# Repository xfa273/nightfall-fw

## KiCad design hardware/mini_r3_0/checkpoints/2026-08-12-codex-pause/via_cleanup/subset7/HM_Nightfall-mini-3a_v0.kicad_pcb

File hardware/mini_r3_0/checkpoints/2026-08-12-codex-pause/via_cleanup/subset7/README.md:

# Integration-safe 7-item drill-in-pad cleanup subset

This subset intentionally excludes the supply/CS-sensitive C_MCU1.2,
C_MCU2.2, C_MCU-M0.2, U4.8, and R33.2 items.

Cleaned items: UBUZ0.2, Q3.2, C7.1, R1FR0.1, R2R0.2, C8.2, Q3.3.

Verified on the fan handoff:

- exact KiCad physical DRC errors: 0
- drill-in-pad overlaps: 5, exactly the five intentionally deferred items
- KiCad unconnected count: 32 (unchanged from input)
- GND groups: 1; GND2 groups: 1
- zone self/cross-edge incidents: 0

Replay with `apply_independent_cleanup.py` using canonical-named project
copies, then run exact refill/DRC/audit again on the integrated board.

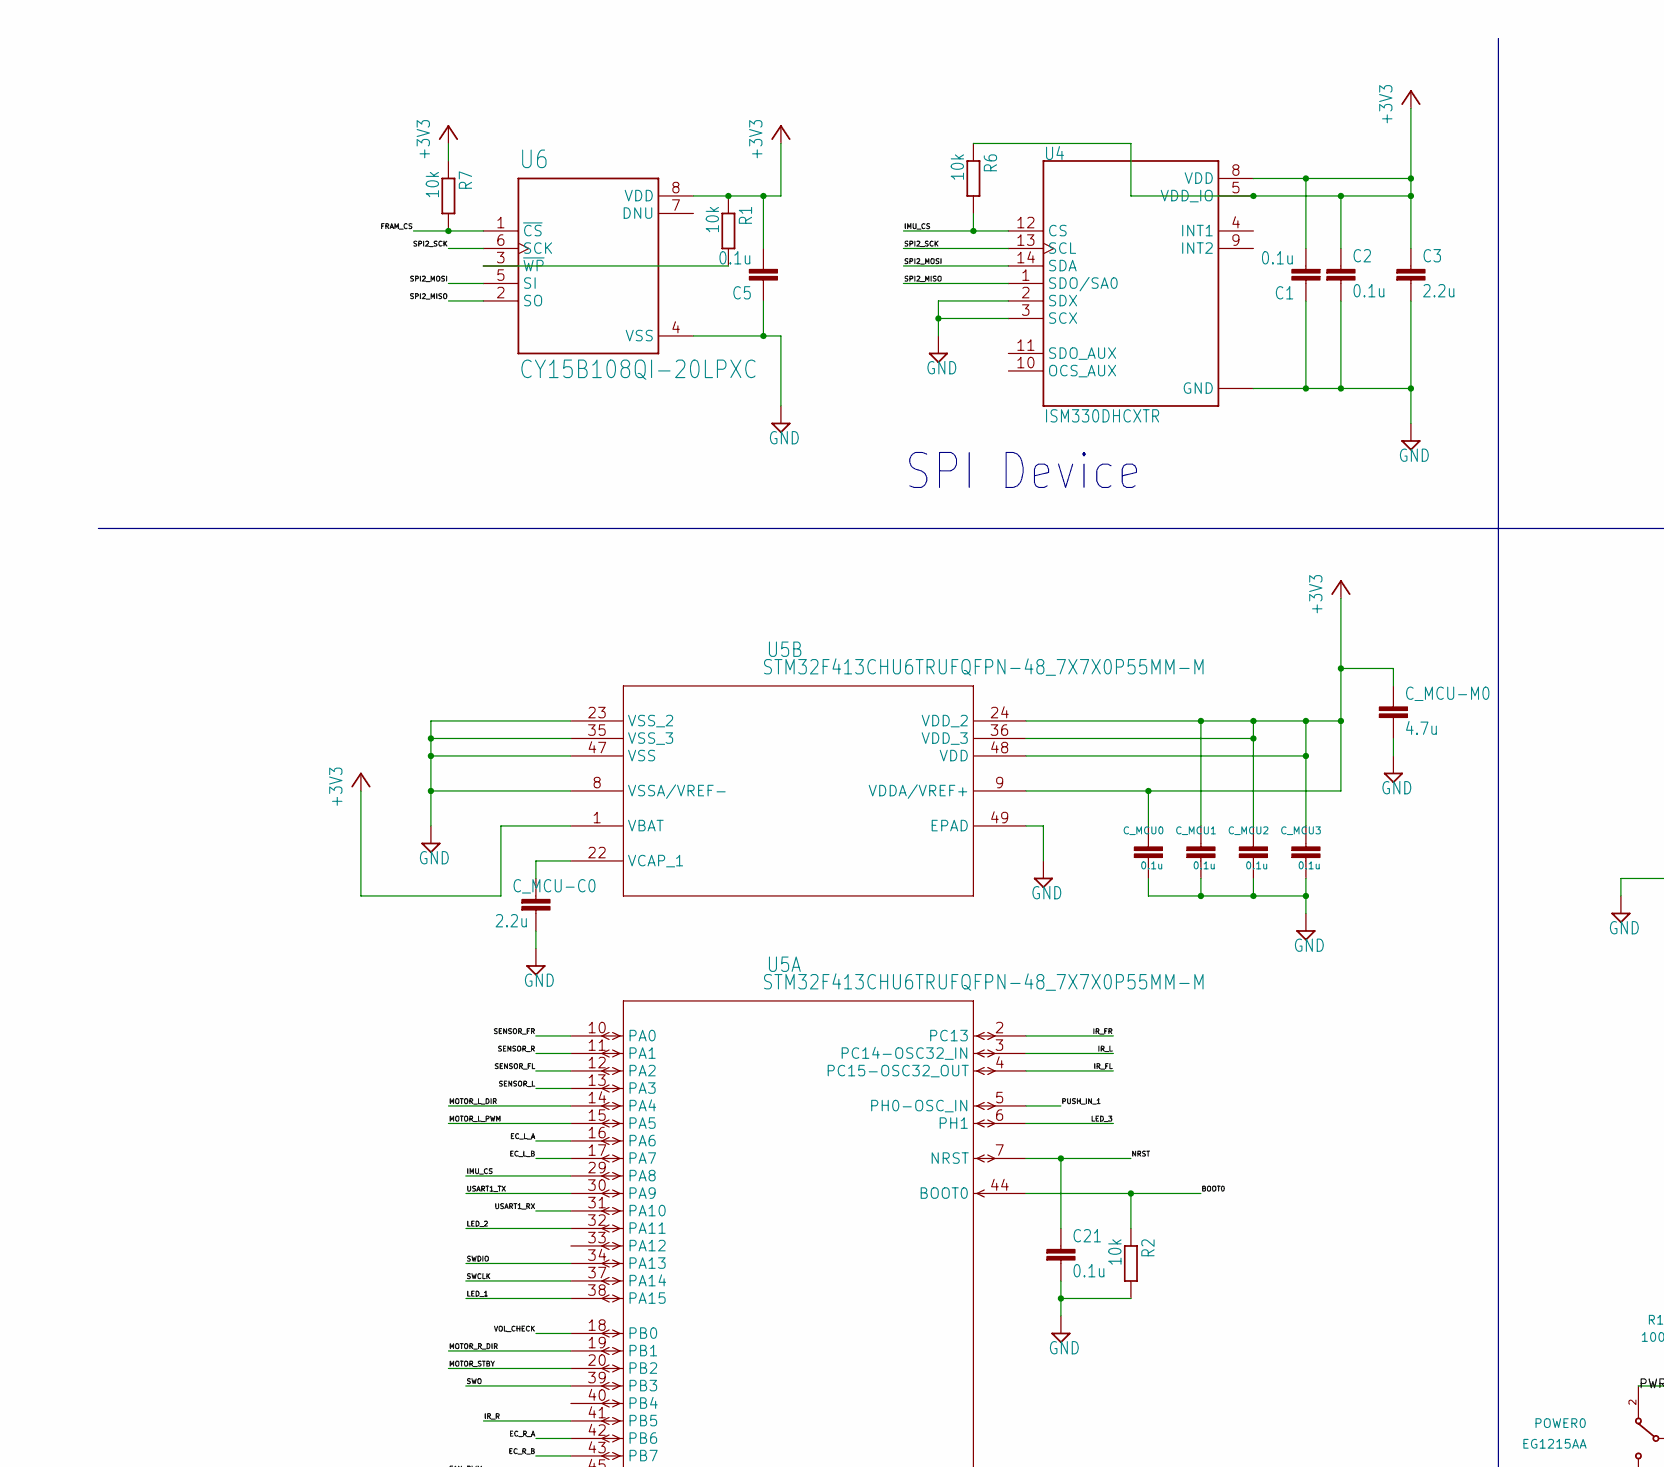
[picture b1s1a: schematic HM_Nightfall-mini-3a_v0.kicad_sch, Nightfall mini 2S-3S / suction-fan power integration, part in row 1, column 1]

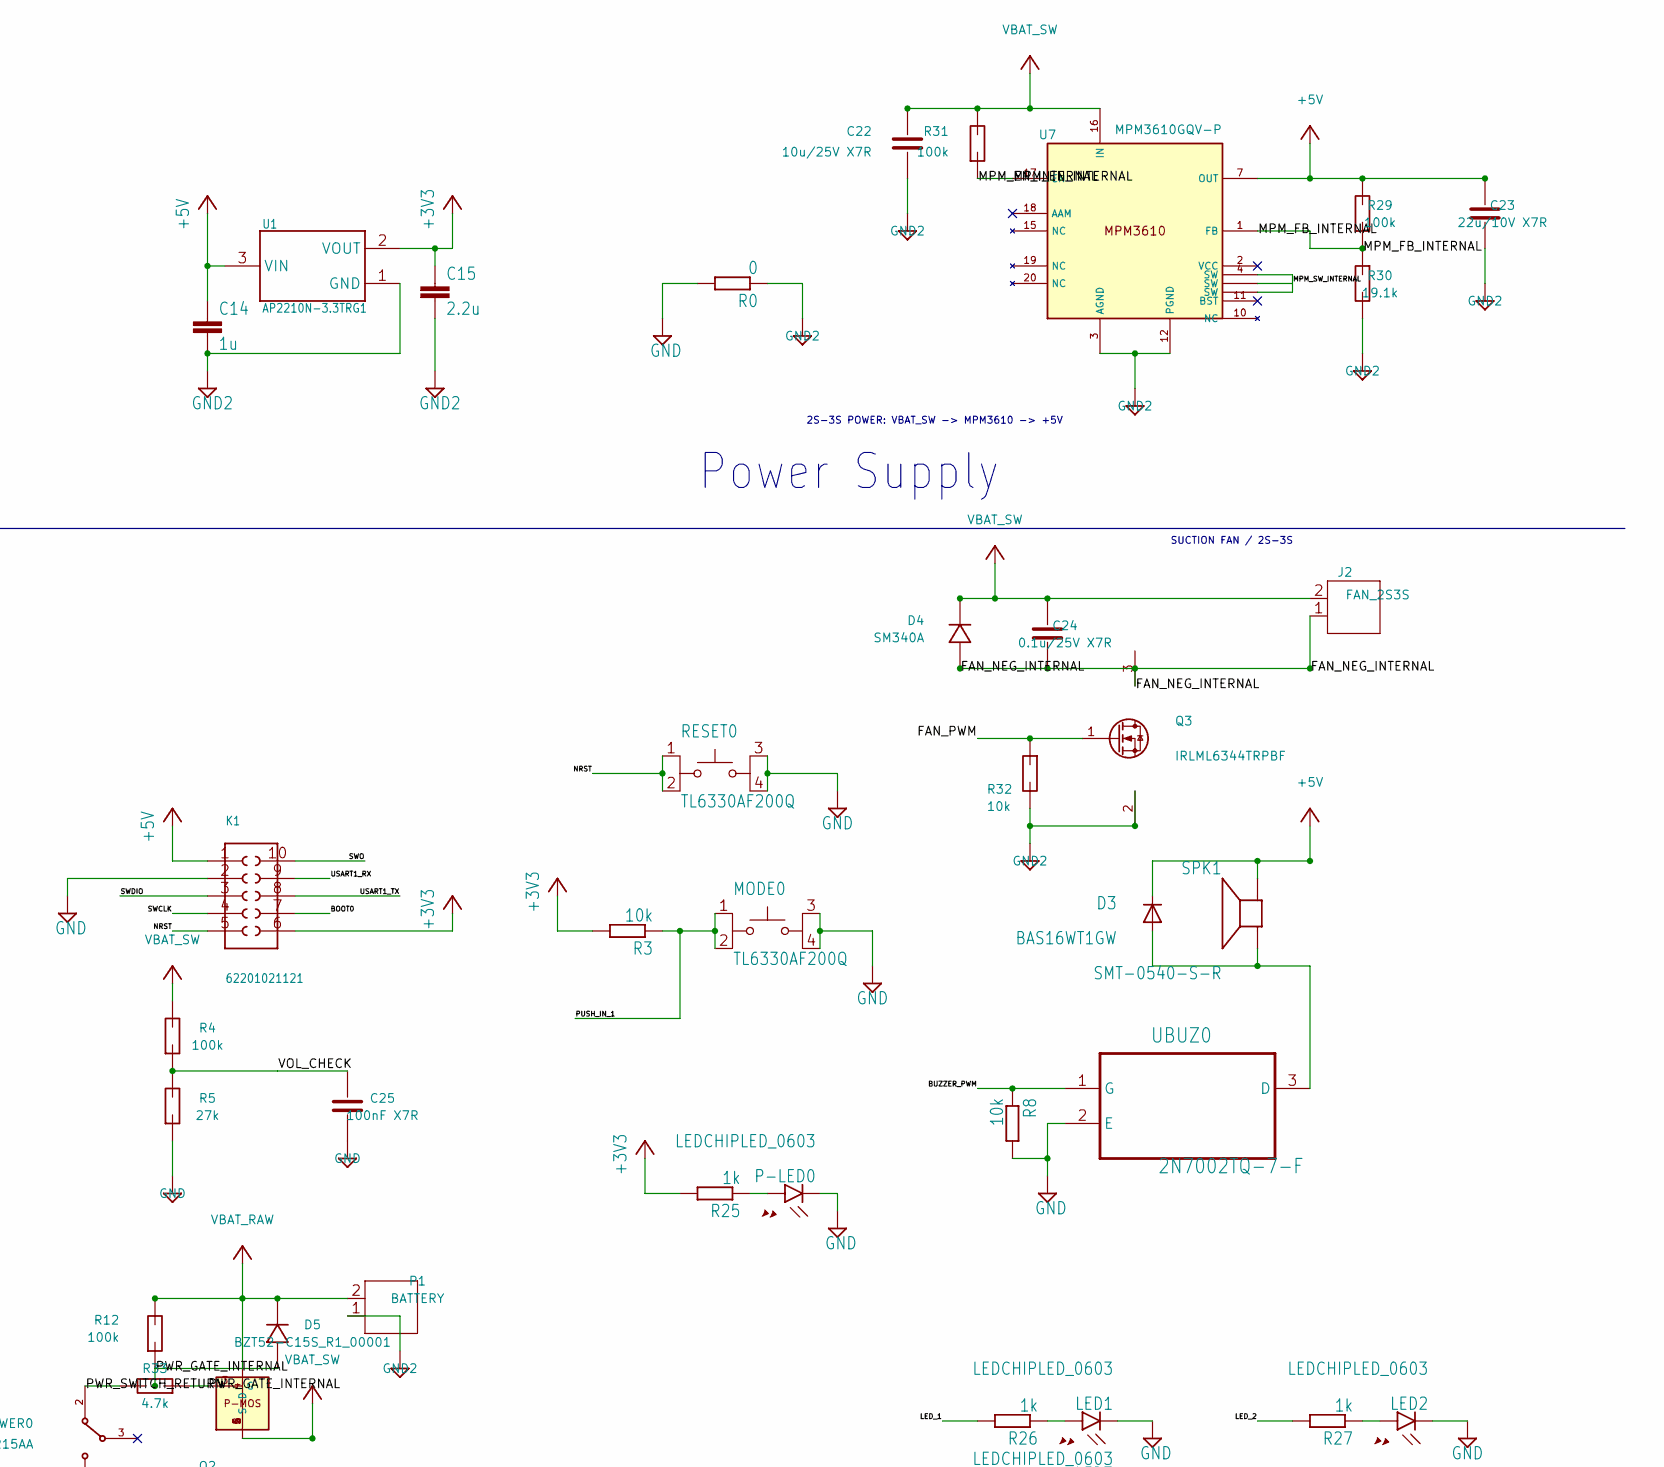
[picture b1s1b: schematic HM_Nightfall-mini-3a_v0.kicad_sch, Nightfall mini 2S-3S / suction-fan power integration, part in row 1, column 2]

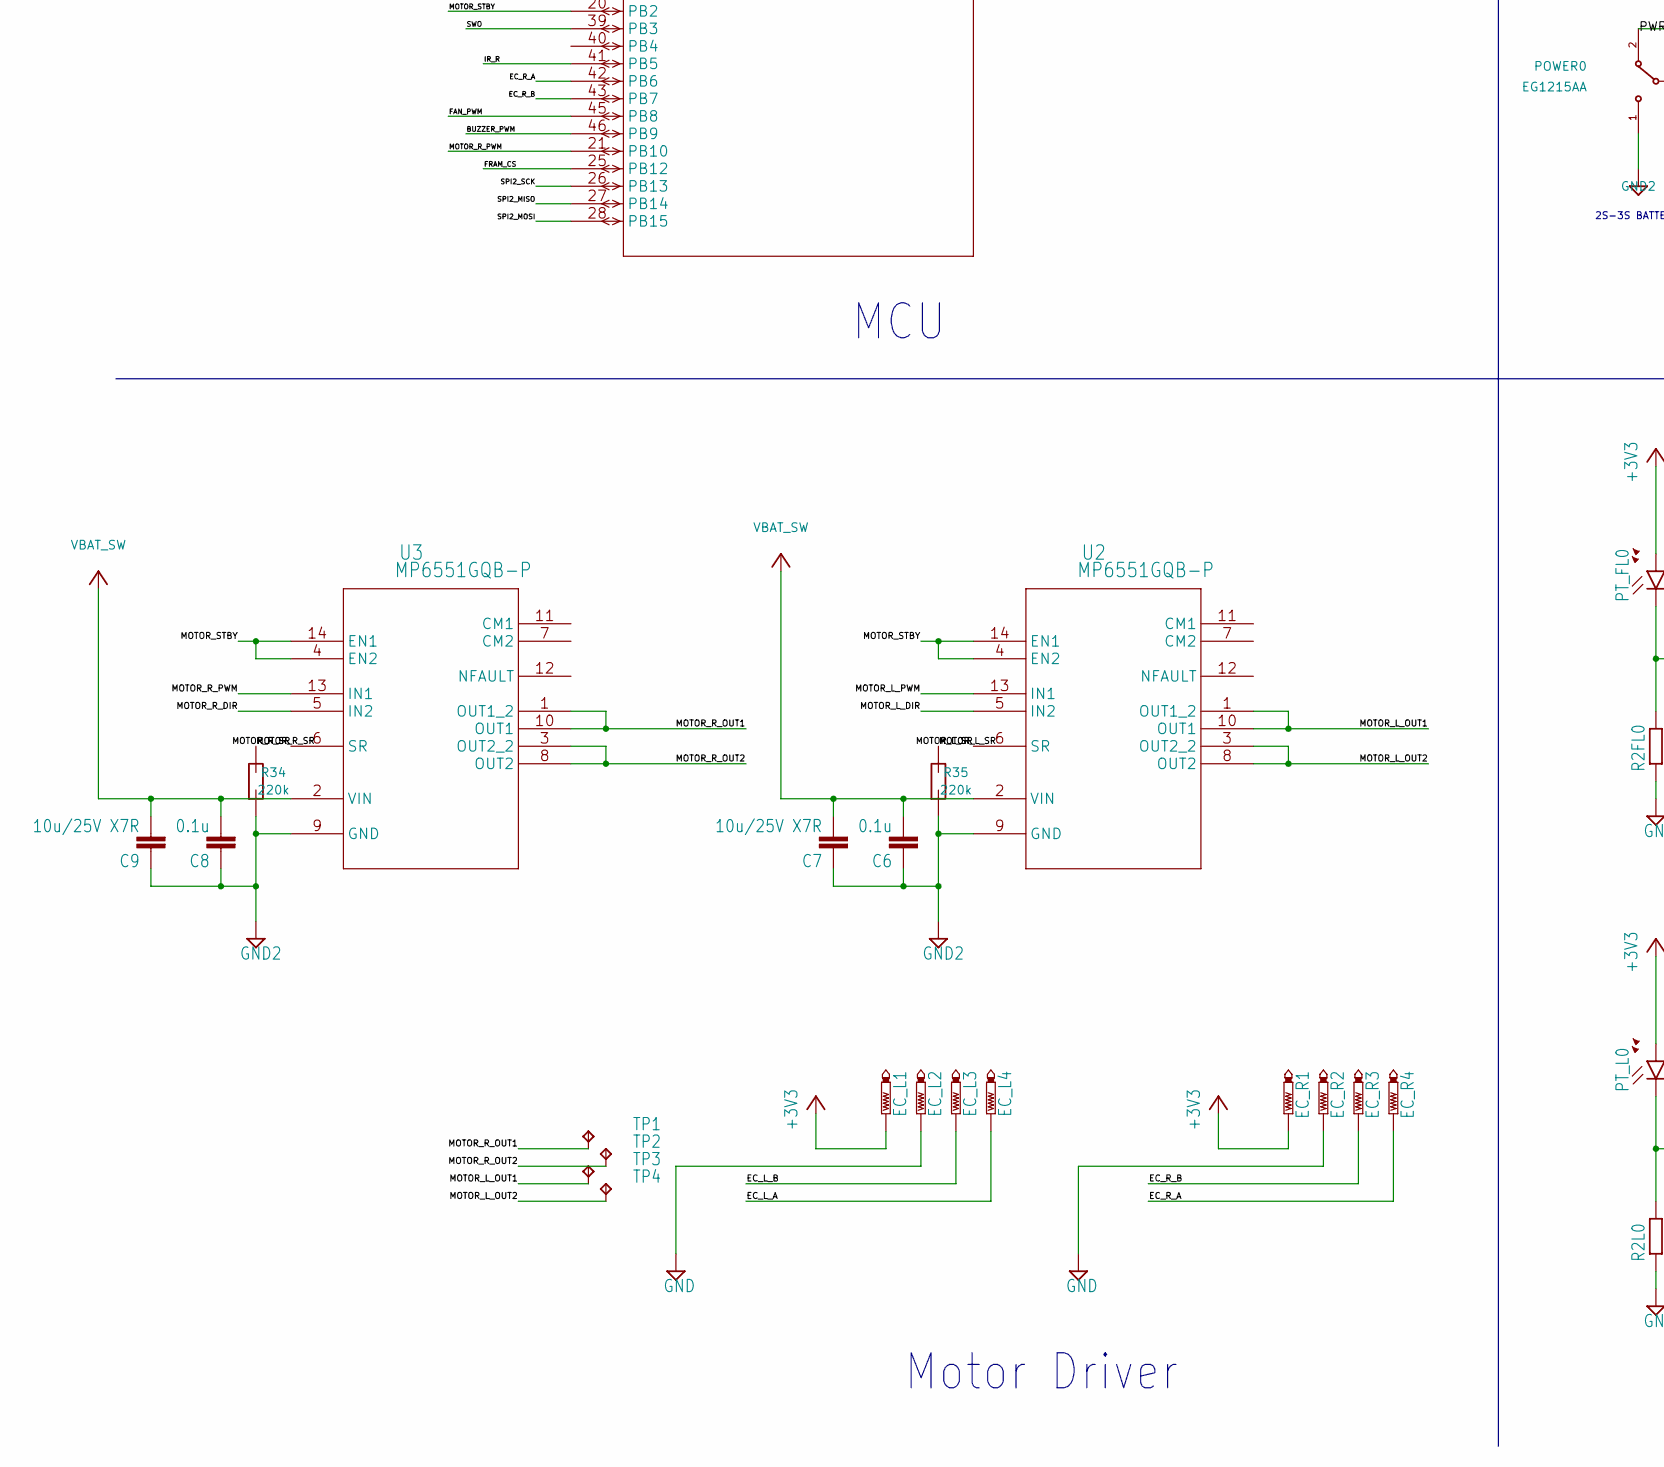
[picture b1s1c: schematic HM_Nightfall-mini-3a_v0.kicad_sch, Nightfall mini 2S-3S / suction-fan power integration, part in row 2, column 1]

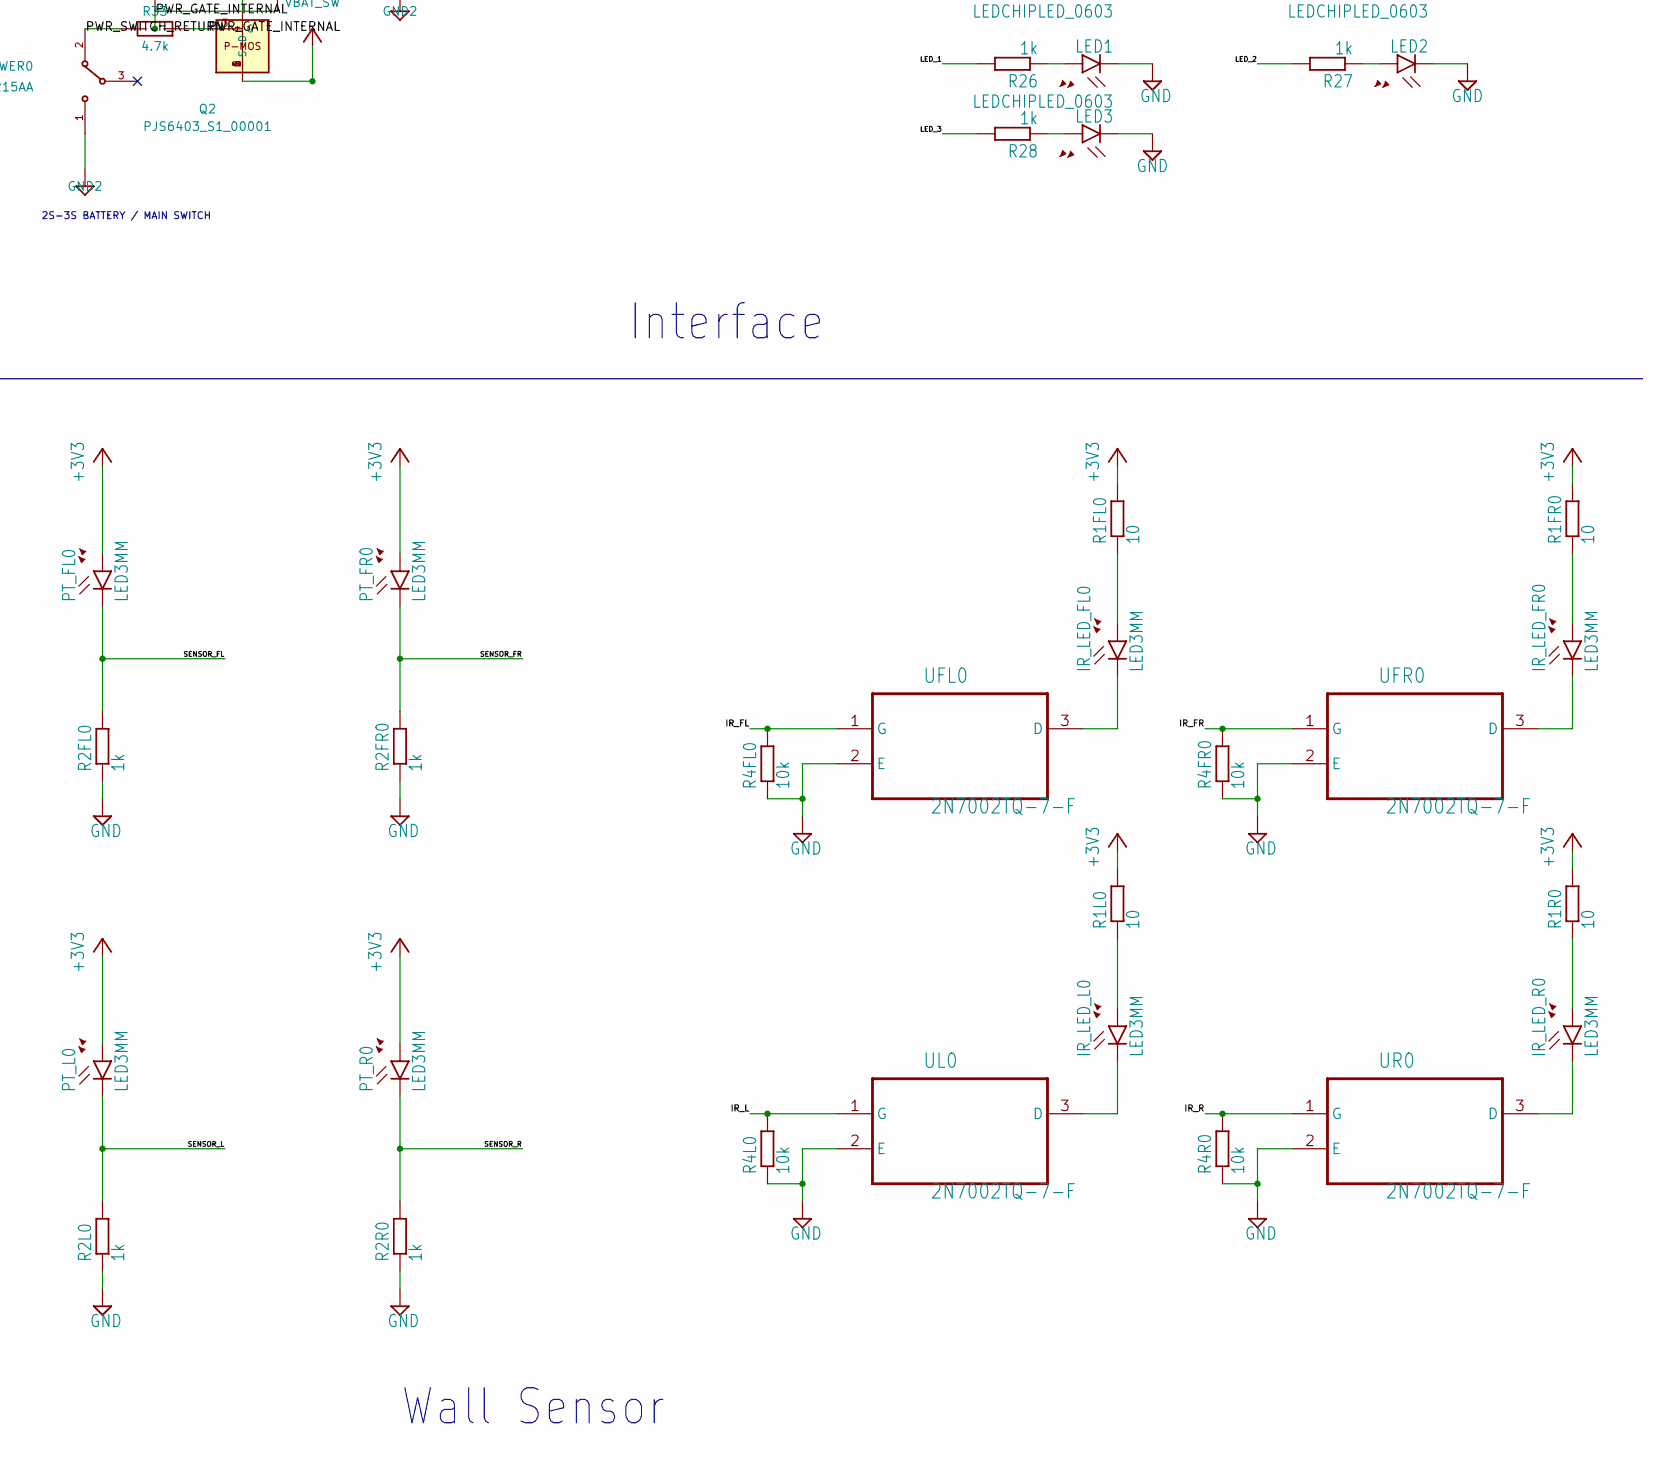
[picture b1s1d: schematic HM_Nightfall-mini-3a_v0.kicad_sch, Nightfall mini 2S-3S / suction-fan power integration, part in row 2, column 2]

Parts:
C1, C2, C5, C6, C8, C21: 0.1u; C0402
C3, C15: 2.2u; C0402
C7, C9, C22: 10u/25V X7R; C_0805_2012Metric
C14: 1u; C0402
C23: 22u/10V X7R; C_0805_2012Metric
C24: 0.1u/25V X7R; C_0402_1005Metric
C25: 100nF X7R; C_0402_1005Metric
C_MCU0, C_MCU2, C_MCU3: 0.1u; C0402
C_MCU1: 0.1u; C_0402_1005Metric
C_MCU-C0: 2.2u; C_0402_1005Metric
C_MCU-M0: 4.7u; C0402
D3: BAS16WT1GW; SOT323
D4: SM340A; D_SMA
D5: BZT52-C15S_R1_00001; D_SOD-323
EC_L1, EC_L2, EC_L3, EC_L4: PTR1TP06SQ; TP06SQ
EC_R1, EC_R2, EC_R3, EC_R4: PTR1TP06SQ; TP06SQ
IR_LED_FL0: LED3MM
IR_LED_FR0: LED3MM
IR_LED_L0: LED3MM
IR_LED_R0: LED3MM
J2: FAN_2S3S; FAN_WIRE_PADS_2P
K1: 62201021121
LED1, LED2, LED3: LEDCHIPLED_0603; CHIPLED_0603
MODE0: TL6330AF200Q; SW_TL6330AF200Q
P1: BATTERY; JST_PH2
P-LED0: LEDCHIPLED_0603; CHIPLED_0603
POWER0: EG1215AA; SW_EG1215AA
PT_FL0: LED3MM
PT_FR0: LED3MM
PT_L0: LED3MM
PT_R0: LED3MM
Q2: PJS6403_S1_00001; SOT-23-6
Q3: IRLML6344TRPBF; SOT-23
R0: 0; R0402
R1, R2, R3, R4FL0, R4FR0, R4L0, R4R0, R6, R7, R8: 10k; R0402
R1FL0, R1FR0, R1L0, R1R0: 10; R0402
R2FL0, R2FR0, R2L0, R2R0, R26, R27, R28: 1k; R0402
R4, R12: 100k; R0402
R5: 27k; R0402
R25: 1k; R_0402_1005Metric
R29, R31: 100k; R_0402_1005Metric
R30: 19.1k; R_0402_1005Metric
R32: 10k; R_0402_1005Metric
R33: 4.7k; R0402
R34, R35: 220k; R_0402_1005Metric
RESET0: TL6330AF200Q; SW_TL6330AF200Q
SPK1: SMT-0540-S-R
TP1, TP2, TP3, TP4: TPB1,27; B1,27
U1: AP2210N-3.3TRG1; SOT95P280X145-3N
U2, U3: MP6551GQB-P; QFN-14_MP6551_MNP
U4: ISM330DHCXTR; PQFN50P250X300X86-14N
U5: STM32F413CHU6TRUFQFPN-48_7X7X0P55MM-M; UFQFPN-48_7X7X0P55MM-M_noEP_hand_solder
U6: CY15B108QI-20LPXC; SON65P328X323X55-8N
U7: MPM3610GQV-P; MPM3610_QFN-20_3x5mm
UBUZ0: 2N7002TQ-7-F; SOT50P160X90-3N
UFL0: 2N7002TQ-7-F; SOT50P160X90-3N
UFR0: 2N7002TQ-7-F; SOT50P160X90-3N
UL0: 2N7002TQ-7-F; SOT50P160X90-3N
UR0: 2N7002TQ-7-F; SOT50P160X90-3N

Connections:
+3V3: C1.2, C2.1, C3.1, C5.2, C15.1, C_MCU0.1, C_MCU1.1, C_MCU2.1, C_MCU3.1, C_MCU-M0.1, EC_L1.TP (TP_TP), EC_R1.TP (TP_TP), K1.6, PT_FL0.A, PT_FR0.A, PT_L0.A, PT_R0.A, R1.1, R1FL0.2, R1FR0.2, R1L0.2, R1R0.2, R3.2, R6.1, R7.1, R25.2, U1.2 (VOUT), U4.5 (VDD_IO), U4.8 (VDD), U5.1 (VBAT), U5.9 (VDDA/VREF+), U5.24 (VDD_2), U5.36 (VDD_3), U5.48 (VDD), U6.8 (VDD)
+5V: C14.1, C23.1, D3.3 (K), K1.1, R29.2, SPK1.+ (-), U1.3 (VIN), U7.7 (OUT), U7.8 (OUT), U7.9 (OUT)
/BOOT0: K1.7, R2.1, U5.44 (BOOT0)
/BUZZER_PWM: R8.1, U5.46 (PB9), UBUZ0.1 (G)
/EC_L_A: EC_L4.TP (TP_TP), U5.16 (PA6)
/EC_L_B: EC_L3.TP (TP_TP), U5.17 (PA7)
/EC_R_A: EC_R4.TP (TP_TP), U5.42 (PB6)
/EC_R_B: EC_R3.TP (TP_TP), U5.43 (PB7)
/FAN_NEG_INTERNAL: C24.2, D4.1 (A), J2.1, Q3.3 (D)
/FAN_PWM: Q3.1 (G), R32.1, U5.45 (PB8)
/IR_FL: R4FL0.2, U5.4 (PC15-OSC32_OUT), UFL0.1 (G)
/IR_FR: R4FR0.2, U5.2 (PC13), UFR0.1 (G)
/IR_L: R4L0.2, U5.3 (PC14-OSC32_IN), UL0.1 (G)
/IR_R: R4R0.2, U5.41 (PB5), UR0.1 (G)
/LED_1: R26.2, U5.38 (PA15)
/LED_2: R27.2, U5.32 (PA11)
/LED_3: R28.2, U5.6 (PH1)
/MOTOR_L_DIR: U2.5 (IN2), U5.14 (PA4)
/MOTOR_L_OUT1: TP3.TP (TP_TP), U2.1 (OUT1_2), U2.10 (OUT1)
/MOTOR_L_OUT2: TP4.TP (TP_TP), U2.3 (OUT2_2), U2.8 (OUT2)
/MOTOR_L_PWM: U2.13 (IN1), U5.15 (PA5)
/MOTOR_L_SR: R35.2, U2.6 (SR)
/MOTOR_R_DIR: U3.5 (IN2), U5.19 (PB1)
/MOTOR_R_OUT1: TP1.TP (TP_TP), U3.1 (OUT1_2), U3.10 (OUT1)
/MOTOR_R_OUT2: TP2.TP (TP_TP), U3.3 (OUT2_2), U3.8 (OUT2)
/MOTOR_R_PWM: U3.13 (IN1), U5.21 (PB10)
/MOTOR_R_SR: R34.2, U3.6 (SR)
/MOTOR_STBY: U2.4 (EN2), U2.14 (EN1), U3.4 (EN2), U3.14 (EN1), U5.20 (PB2)
/MPM_EN_INTERNAL: R31.1, U7.17 (EN)
/MPM_FB_INTERNAL: R29.1, R30.1, U7.1 (FB)
/MPM_SW_INTERNAL: U7.4 (SW), U7.5 (SW), U7.6 (SW)
/NRST: C21.1, K1.5, RESET0.1, RESET0.2, U5.7 (NRST)
/PUSH_IN_1: MODE0.1, MODE0.2, R3.1, U5.5 (PH0-OSC_IN)
/PWR_GATE_INTERNAL: D5.1 (A), Q2.3 (G), R12.1, R33.1
/PWR_SWITCH_RETURN: POWER0.2 (COM), R33.2
/SENSOR_FL: PT_FL0.K (C), R2FL0.2, U5.12 (PA2)
/SENSOR_FR: PT_FR0.K (C), R2FR0.2, U5.10 (PA0)
/SENSOR_L: PT_L0.K (C), R2L0.2, U5.13 (PA3)
/SENSOR_R: PT_R0.K (C), R2R0.2, U5.11 (PA1)
/SPI2_MISO: U4.1 (SDO/SA0), U5.27 (PB14), U6.2 (SO)
/SPI2_MOSI: U4.14 (SDA), U5.28 (PB15), U6.5 (SI)
/SPI2_SCK: U4.13 (SCL), U5.26 (PB13), U6.6 (SCK)
/SWCLK: K1.4, U5.37 (PA14)
/SWDIO: K1.3, U5.34 (PA13)
/SWO: K1.10, U5.39 (PB3)
/USART1_RX: K1.9, U5.31 (PA10)
/USART1_TX: K1.8, U5.30 (PA9)
/VOL_CHECK: C25.1, R4.1, R5.2, U5.18 (PB0)
GND: C1.1, C2.2, C3.2, C5.1, C21.2, C25.2, C_MCU0.2, C_MCU1.2, C_MCU2.2, C_MCU3.2, C_MCU-C0.2, C_MCU-M0.2, EC_L2.TP (TP_TP), EC_R2.TP (TP_TP), K1.2, LED1.C, LED2.C, LED3.C, MODE0.3, MODE0.4, P-LED0.C, R0.2, R2.2, R2FL0.1, R2FR0.1, R2L0.1, R2R0.1, R4FL0.1, R4FR0.1, R4L0.1, R4R0.1, R5.1, R8.2, RESET0.3, RESET0.4, U4.2 (SDX), U4.3 (SCX), U4.6 (GND), U4.7 (GND), U5.8 (VSSA/VREF-), U5.23 (VSS_2), U5.35 (VSS_3), U5.47 (VSS), U5.49 (EPAD), U6.4 (VSS), UBUZ0.2 (E), UFL0.2 (E), UFR0.2 (E), UL0.2 (E), UR0.2 (E)
GND2: C6.1, C7.1, C8.1, C9.1, C14.2, C15.2, C22.2, C23.2, P1.1, POWER0.1 (OFF), Q3.2 (S), R0.1, R30.2, R32.2, R34.1, R35.1, U1.1 (GND), U2.9 (GND), U3.9 (GND), U7.3 (AGND), U7.12 (PGND), U7.13 (PGND), U7.14 (PGND)
unnamed: D3.1 (A), SPK1.- (+), UBUZ0.3 (D)
unnamed: IR_LED_FL0.K (C), UFL0.3 (D)
unnamed: IR_LED_FL0.A, R1FL0.1
unnamed: IR_LED_FR0.K (C), UFR0.3 (D)
unnamed: IR_LED_FR0.A, R1FR0.1
unnamed: IR_LED_L0.K (C), UL0.3 (D)
unnamed: IR_LED_L0.A, R1L0.1
unnamed: IR_LED_R0.K (C), UR0.3 (D)
unnamed: IR_LED_R0.A, R1R0.1
unnamed: LED1.A, R26.1
unnamed: LED2.A, R27.1
unnamed: LED3.A, R28.1
unnamed: P-LED0.A, R25.1
unnamed: C_MCU-C0.1, U5.22 (VCAP_1)
unnamed: R1.2, U6.3 (~WP)
VBAT_RAW: D5.2 (K), P1.2, Q2.4 (S), R12.2
VBAT_SW: C6.2, C7.2, C8.2, C9.2, C22.1, C24.1, D4.2 (K), J2.2, Q2.1 (D), Q2.2 (D), Q2.5 (D), Q2.6 (D), R4.2, R31.2, U2.2 (VIN), U3.2 (VIN), U7.16 (IN)

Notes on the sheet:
Wall Sensor
MCU
Power Supply
SPI Device
Interface
Motor Driver
2S-3S POWER: VBAT_SW -> MPM3610 -> +5V
SUCTION FAN / 2S-3S
2S-3S BATTERY / MAIN SWITCH

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
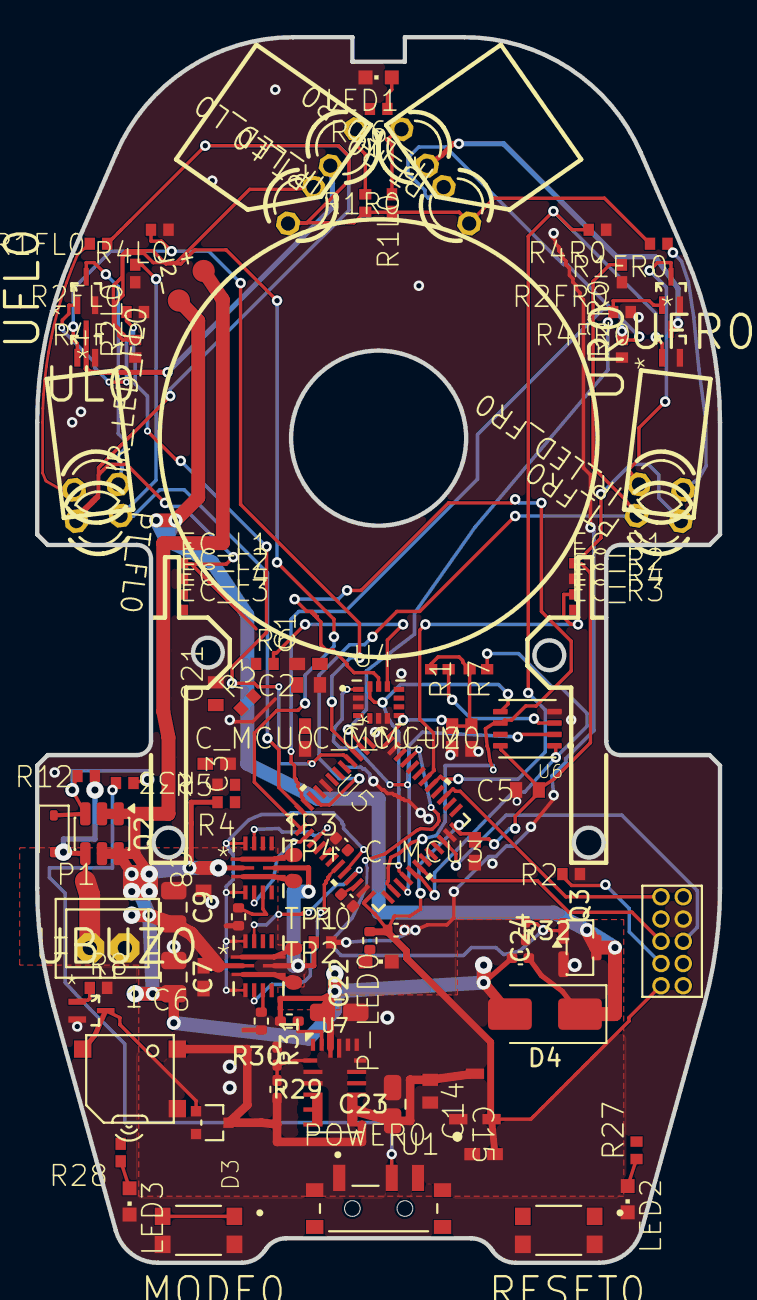
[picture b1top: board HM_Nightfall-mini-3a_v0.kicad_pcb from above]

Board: 2 copper layers, 39.0 x 70.0 mm, 102 parts (0 on the bottom side), 69 nets.
